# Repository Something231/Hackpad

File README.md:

# Hackpad
Hack club starter project based on https://blueprint.hackclub.com/starter-projects/hackpad

This is just gonna be a circular devboard with a small dial in the centre for volume control.

Just making this to learn a bit more about doing circuit design mostly.

Repository includes:
- Kicad files in /PCB(kicad) 
- Raw Gerber in /gerber , also in CAD/gerber.zip
- Hackpad case 3d files in stl, step and f3d formats in /CAD

Pcb images:

3d Model:

Assembled 3d Model that took ages to make:

For some reason I couldnt update what I put before for cart screenshots, so:
I need Usd$3.50:

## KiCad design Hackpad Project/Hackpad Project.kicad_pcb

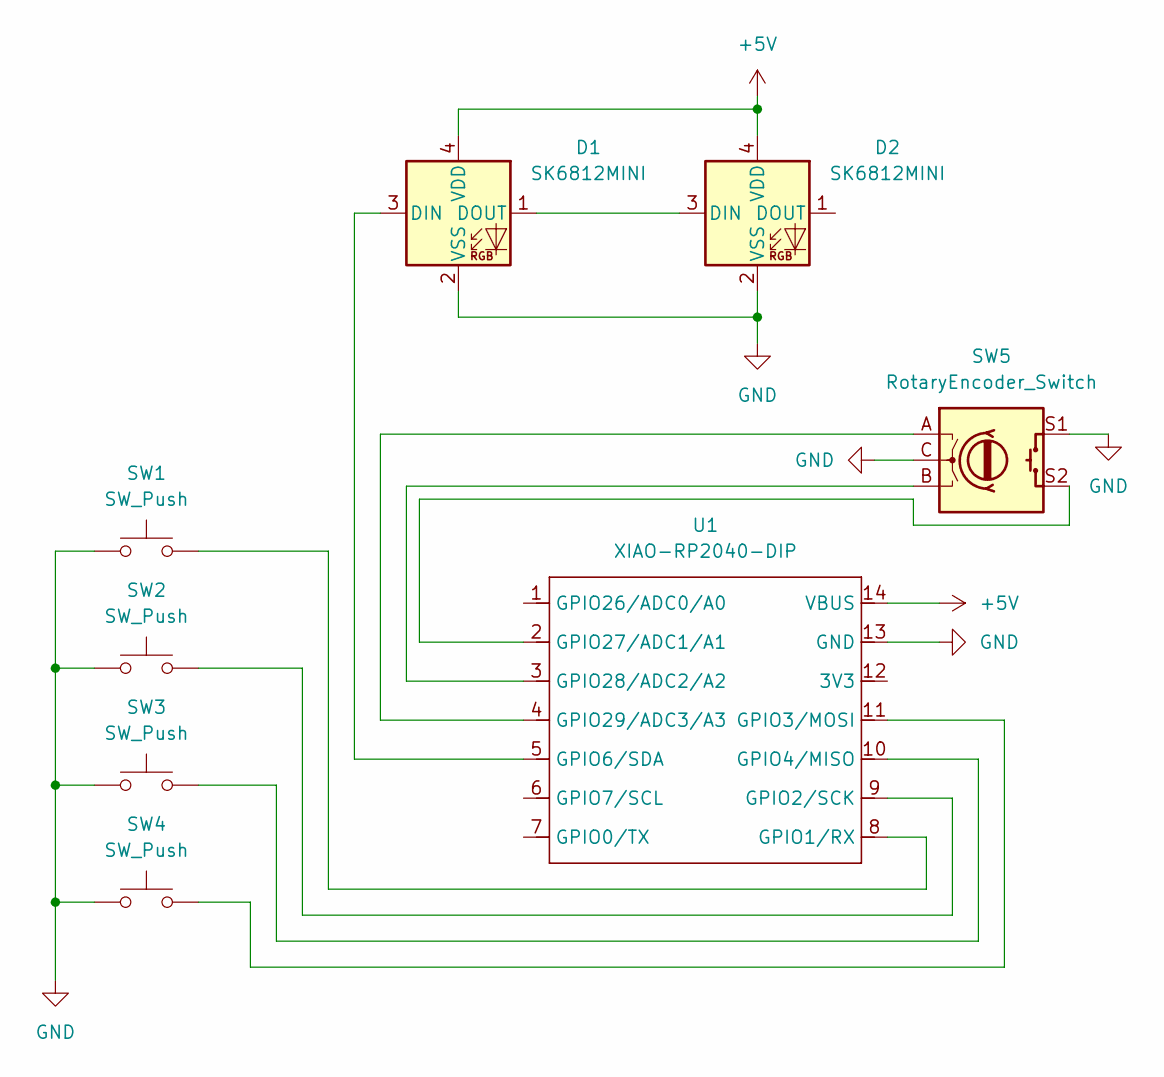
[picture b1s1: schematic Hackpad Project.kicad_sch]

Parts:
D1, D2: SK6812MINI; LED_SK6812MINI_PLCC4_3.5x3.5mm_P1.75mm
SW1, SW2, SW3, SW4: SW_Push; SW_Cherry_MX_1.00u_PCB
SW5: RotaryEncoder_Switch; RotaryEncoder_Alps_EC11E-Switch_Vertical_H20mm
U1: XIAO-RP2040-DIP

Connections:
+5V: D1.4 (VDD), D2.4 (VDD), U1.14 (VBUS)
GND: D1.2 (VSS), D2.2 (VSS), SW1.1, SW2.1, SW3.1, SW4.1, SW5.C, SW5.S1, U1.13 (GND)
unnamed: D1.3 (DIN), U1.5 (GPIO6/SDA)
unnamed: D1.1 (DOUT), D2.3 (DIN)
unnamed: SW1.2, U1.8 (GPIO1/RX)
unnamed: SW2.2, U1.9 (GPIO2/SCK)
unnamed: SW4.2, U1.11 (GPIO3/MOSI)
unnamed: SW3.2, U1.10 (GPIO4/MISO)
unnamed: SW5.S2, U1.2 (GPIO27/ADC1/A1)
unnamed: SW5.B, U1.3 (GPIO28/ADC2/A2)
unnamed: SW5.A, U1.4 (GPIO29/ADC3/A3)

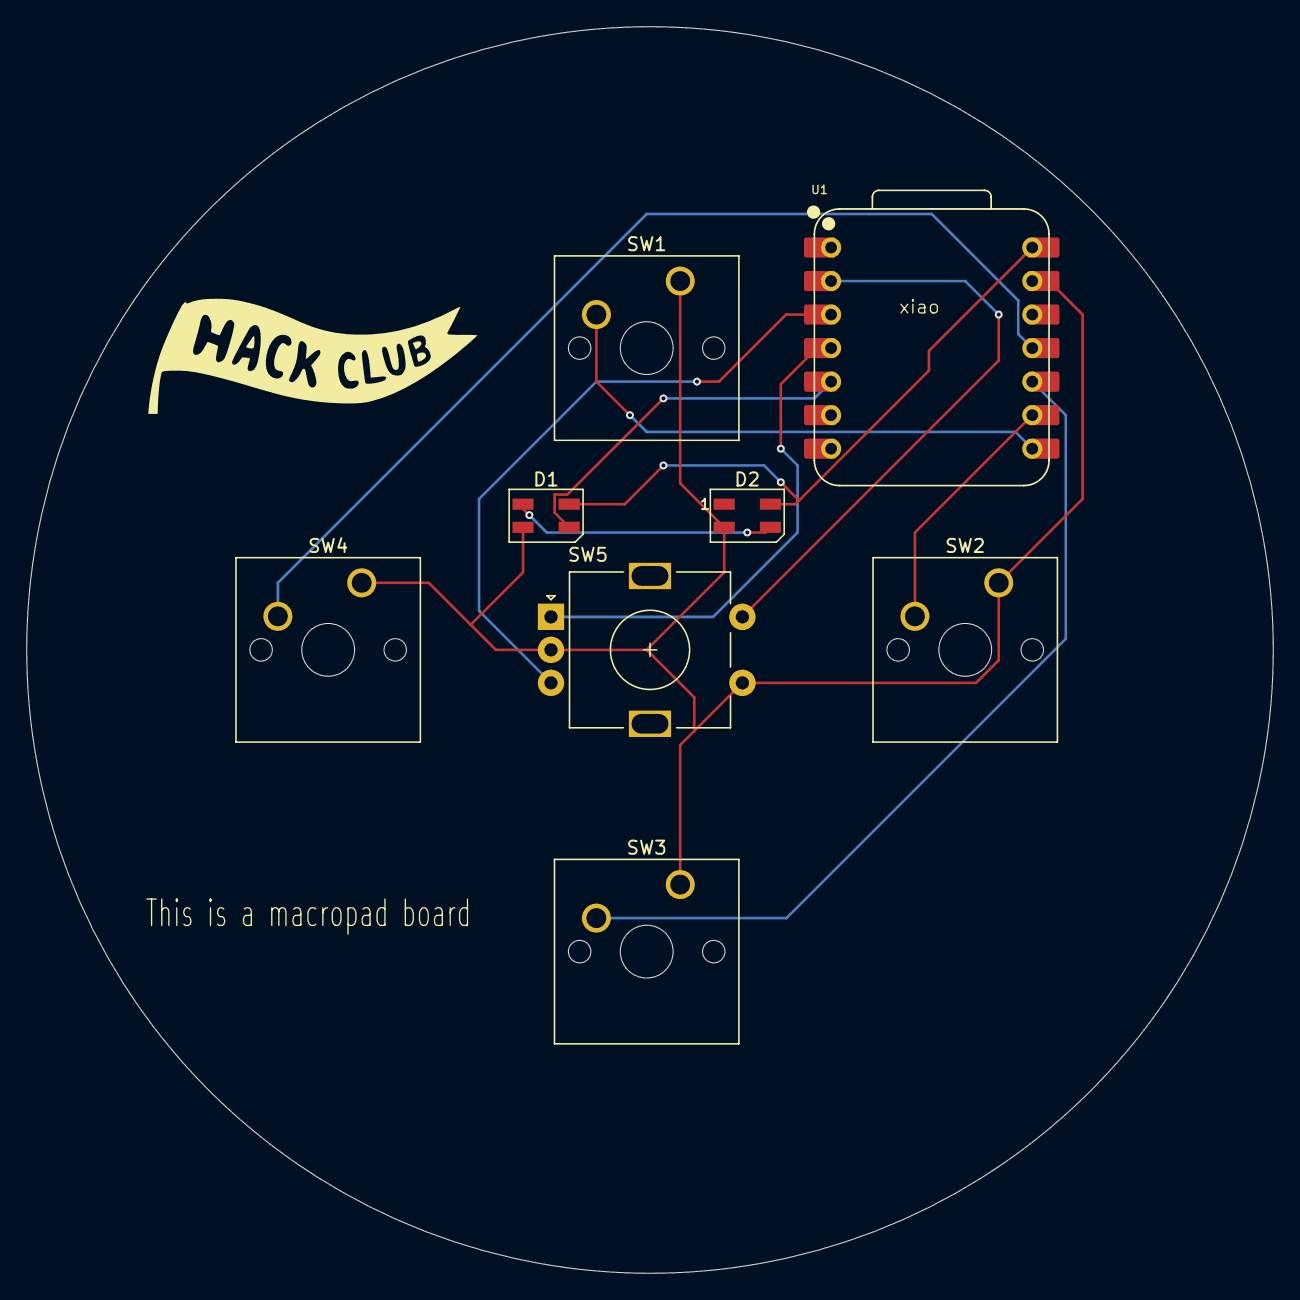
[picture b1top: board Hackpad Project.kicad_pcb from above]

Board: 2 copper layers, 94.4 x 94.4 mm, 8 parts (0 on the bottom side), 11 nets.

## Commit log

2025-11-12 did a little
2025-11-12 Rename Screenshot from 2025-11-12 20-51-51.png to Screenshot of board layout
2025-11-12 Rename Screenshot from 2025-11-12 20-52-21.png to Screenshot of Schematic
2025-11-12 Rename Screenshot of board layout to Screenshot of board layout.png
2025-11-12 Rename Screenshot of Schematic to Screenshot of Schematic.png
2025-11-13 Rename Hackpad.f3d to Hackpad_bottom.f3d
2025-11-13 Rename plate-2025-11-12T12_27_52.f3d to hackpad_top.f3d
2025-11-13 Fix formatting of project file sections in README
2025-11-13 Include images for PCB and 3D model in README
    Added PCB and 3D model images to the README.
2025-11-13 Update README to include learning objectives
    Added a note about learning circuit design.
2025-11-13 Reorganised files
2025-11-14 hopefully this is good enough...
2025-11-14 Add assembled 3D model images to README
    Added assembled 3D model screenshots to README.
2025-11-14 Add screenshot of assembled 3D model to README
    Added a new screenshot of the assembled 3D model.
2025-11-14 Update README with new cart screenshots and pricing
    Added new cart screenshots and updated pricing information.
2025-11-19 For some reason there was no drill insructions, fixed
